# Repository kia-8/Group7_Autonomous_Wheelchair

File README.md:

# Group7_Autonomous_Wheelchair
SPRO3 - Autonomous wheelchair for passenger transport in airports

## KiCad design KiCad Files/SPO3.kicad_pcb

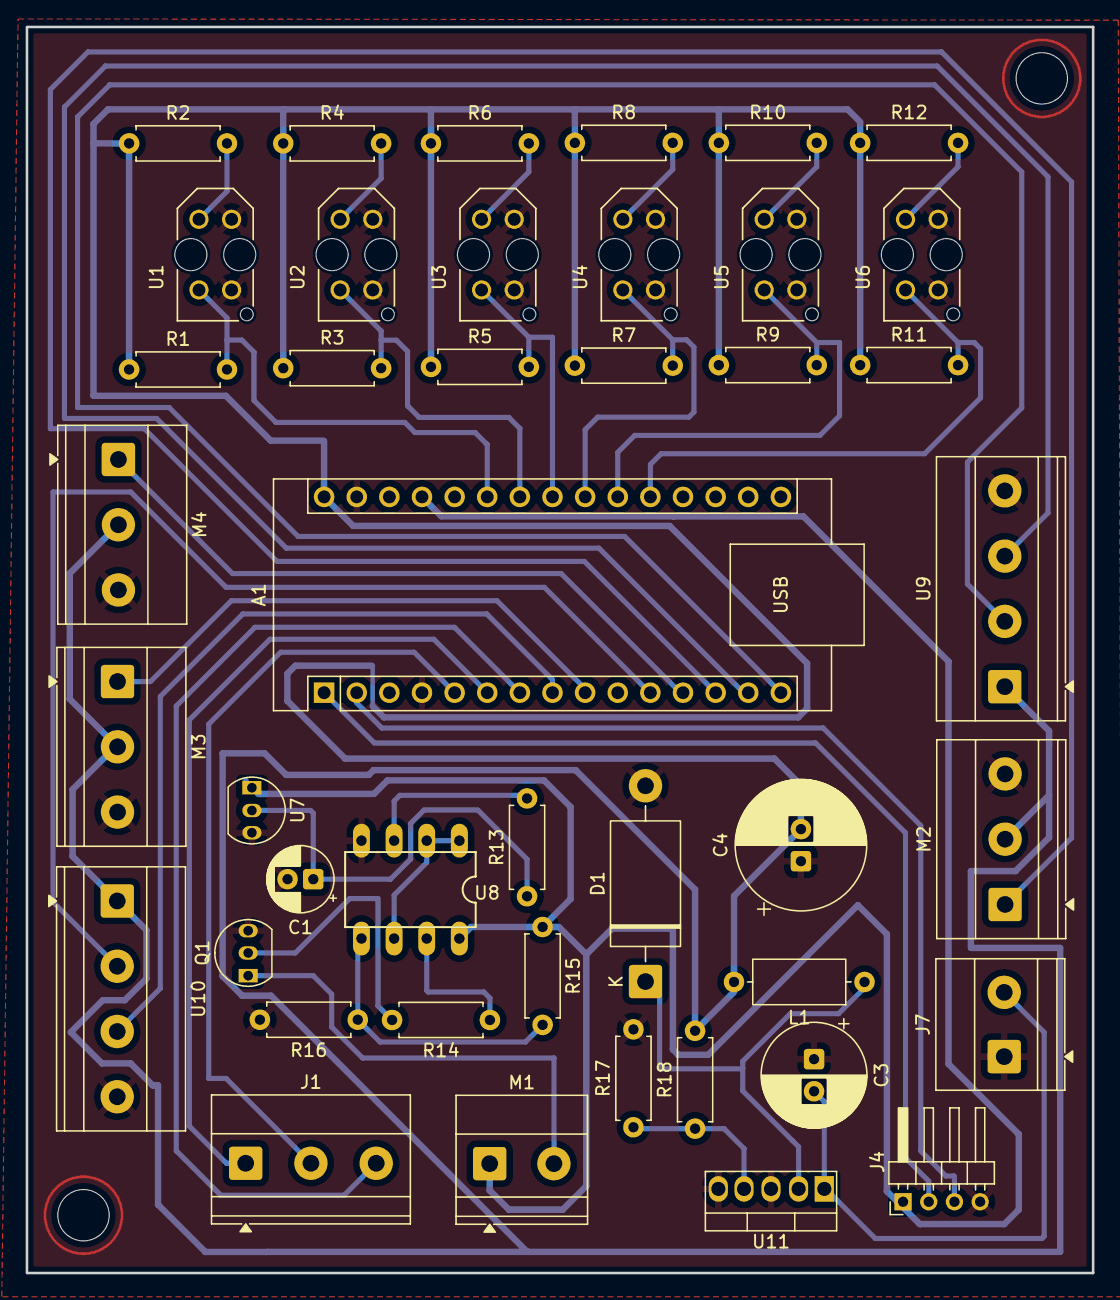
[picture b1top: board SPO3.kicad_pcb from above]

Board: 2 copper layers, 83.0 x 97.0 mm, 43 parts (0 on the bottom side), 37 nets.

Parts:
A1: Arduino_Nano_v3.x; Arduino_Nano
C1: 10p; CP_Radial_D5.0mm_P2.00mm
C3: 470u; CP_Radial_D8.0mm_P2.50mm
C4: 1000u; CP_Radial_D10.0mm_P2.50mm
D1: 1N5822; D_DO-201_P15.24mm_Horizontal
J1: Screw_Terminal_01x03; TerminalBlock_Phoenix_MKDS-1,5-3-5.08_1x03_P5.08mm_Horizont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
J4: Conn_01x04_Pin; PinHeader_1x04_P2.00mm_Horizontal
J7: Screw_Terminal_01x02; TerminalBlock_Phoenix_MKDS-1,5-2_1x02_P5.00mm_Horizontal
L1: 470u; L_Axial_L7.0mm_D3.3mm_P10.16mm_Horizontal_Fastron_MICC
M1: Fan; TerminalBlock_Phoenix_MKDS-1,5-2_1x02_P5.00mm_Horizontal
M2, M3, M4: Motor_Servo; TerminalBlock_Phoenix_MKDS-1,5-3-5.08_1x03_P5.08mm_Horizont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
Q1: BC547; TO-92_Inline NEWW
R1, R3, R9, R11: 4.7k; R_Axial_DIN0207_L6.3mm_D2.5mm_P7.62mm_Horizontal
R2, R4, R6, R8, R10, R12: 180; R_Axial_DIN0207_L6.3mm_D2.5mm_P7.62mm_Horizontal
R5, R7, R13, R14: 10k; R_Axial_DIN0207_L6.3mm_D2.5mm_P7.62mm_Horizontal
R15: 9k; R_Axial_DIN0207_L6.3mm_D2.5mm_P7.62mm_Horizontal
R16, R17: 1k; R_Axial_DIN0207_L6.3mm_D2.5mm_P7.62mm_Horizontal
R18: 2.7k; R_Axial_DIN0207_L6.3mm_D2.5mm_P7.62mm_Horizontal
U1, U2, U3, U4, U5, U6: TCRT5000; OPTO_TCRT5000
U7: LM35-LP; TO-92_Inline New
U8: LM358; DIL08
U9, U10: HC-SR04; TerminalBlock_Phoenix_MKDS-1,5-4-5.08_1x04_P5.08mm_Horizont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
U11: LM2576HVT-ADJ; TO-220-5_Vertical New222

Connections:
+5V: A1.27 (+5V), J4.1, M1.1 (+), R15.1, U7.1 (+V_{S}), U8.8 (V+)
+9V: C3.2, J7.2, U11.1 (VIN)
/Vout: A1.30 (VIN), C4.2, L1.2, M2.2 (+), M3.2 (+), M4.2 (+), R1.1, R2.1, R3.1, R4.1, R5.1, R6.1, R7.1, R8.1, R9.1, R10.1, R11.1, R12.1, R18.2, U9.1 (VCC), U10.1 (VCC)
GND: A1.4 (GND), A1.29 (GND), C1.2, C3.1, C4.1, D1.2 (A), J4.4, J7.1, M2.3 (-), M3.3 (-), M4.3 (-), Q1.3 (E), R16.2, R17.2, U1.CATH, U1.E, U2.CATH, U2.E, U3.CATH, U3.E, U4.CATH, U4.E, U5.CATH, U5.E, U6.CATH, U6.E, U7.3 (GND), U8.4 (V-), U9.4 (GND), U10.4 (GND), U11.3 (GND), U11.5 (~ON/OFF)
unnamed: A1.20 (A1), R11.2, U6.COLL
unnamed: A1.21 (A2), R9.2, U5.COLL
unnamed: A1.22 (A3), R7.2, U4.COLL
unnamed: A1.23 (A4), R5.2, U3.COLL
unnamed: A1.24 (A5), R3.2, U2.COLL
unnamed: A1.25 (A6), R1.2, U1.COLL
unnamed: A1.2 (D0/RX), J4.3
unnamed: A1.1 (D1/TX), J4.2
unnamed: A1.5 (D2), J1.2
unnamed: A1.6 (D3), J1.1
unnamed: A1.7 (D4), J1.3
unnamed: A1.8 (D5), U10.3 (ECHO)
unnamed: A1.9 (D6), M3.1 (PWM)
unnamed: A1.11 (D8), U10.2 (TRIG)
unnamed: A1.12 (D9), M4.1 (PWM)
unnamed: A1.13 (D10), M2.1 (PWM)
unnamed: A1.14 (D11), U9.3 (ECHO)
unnamed: A1.15 (D12), U9.2 (TRIG)
unnamed: D1.1 (K), L1.1, U11.2 (OUT)
unnamed: M1.2 (-), Q1.1 (C)
unnamed: Q1.2 (B), R14.2
unnamed: R2.2, U1.A
unnamed: R4.2, U2.A
unnamed: R6.2, U3.A
unnamed: R8.2, U4.A
unnamed: R10.2, U5.A
unnamed: R12.2, U6.A
unnamed: R14.1, U8.7
unnamed: C1.1, R13.1, U7.2 (V_{OUT})
unnamed: R13.2, U8.3 (+)
unnamed: U8.1, U8.2 (-), U8.6 (-)
unnamed: R15.2, R16.1, U8.5 (+)
unnamed: R17.1, R18.1, U11.4 (FB)

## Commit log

2025-12-23 Create temp
2025-12-23 Create Electrical Circuit
2025-12-23 Create Electrical Circuits
2025-12-23 Create Technical Drawing
